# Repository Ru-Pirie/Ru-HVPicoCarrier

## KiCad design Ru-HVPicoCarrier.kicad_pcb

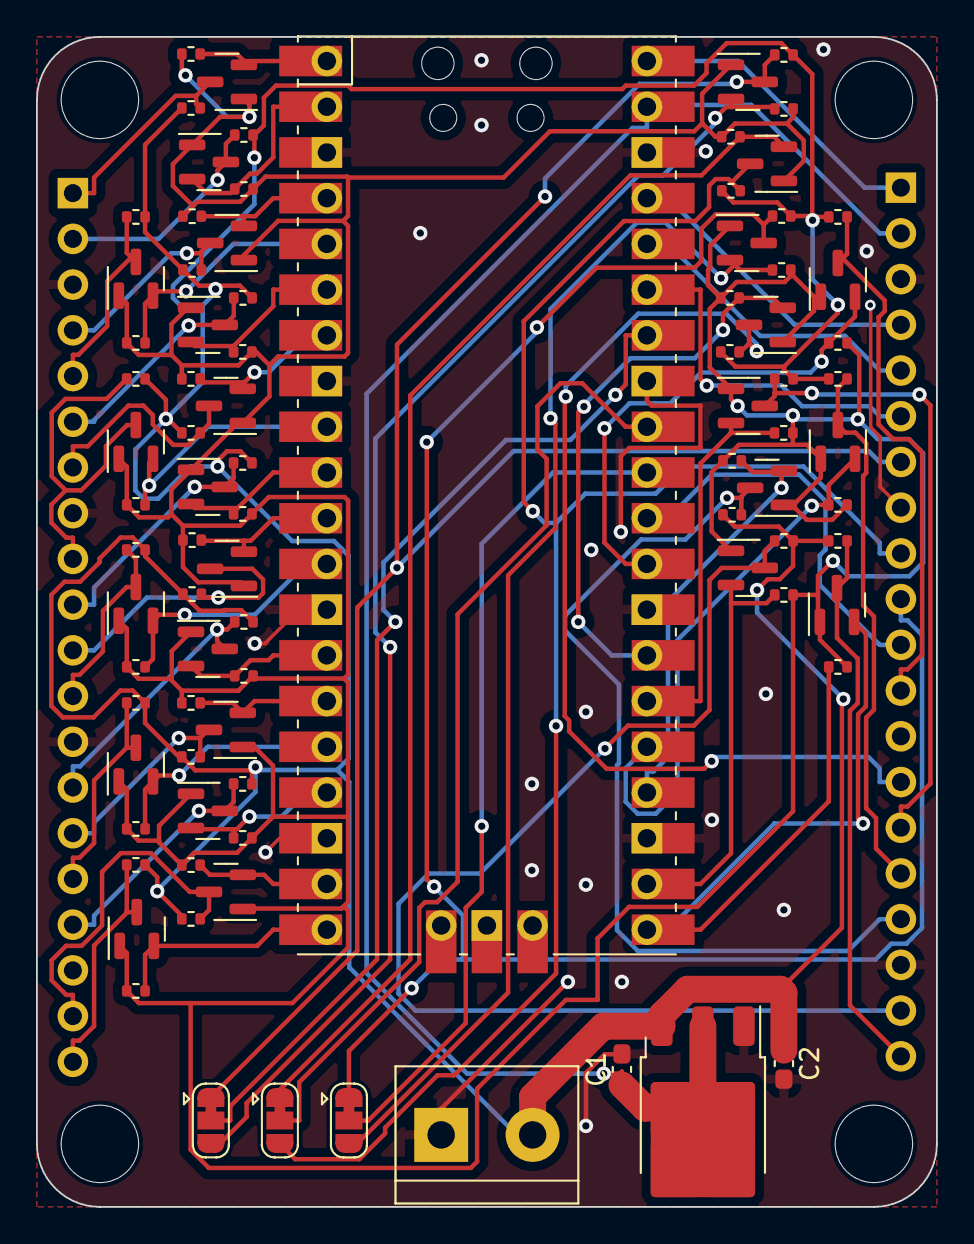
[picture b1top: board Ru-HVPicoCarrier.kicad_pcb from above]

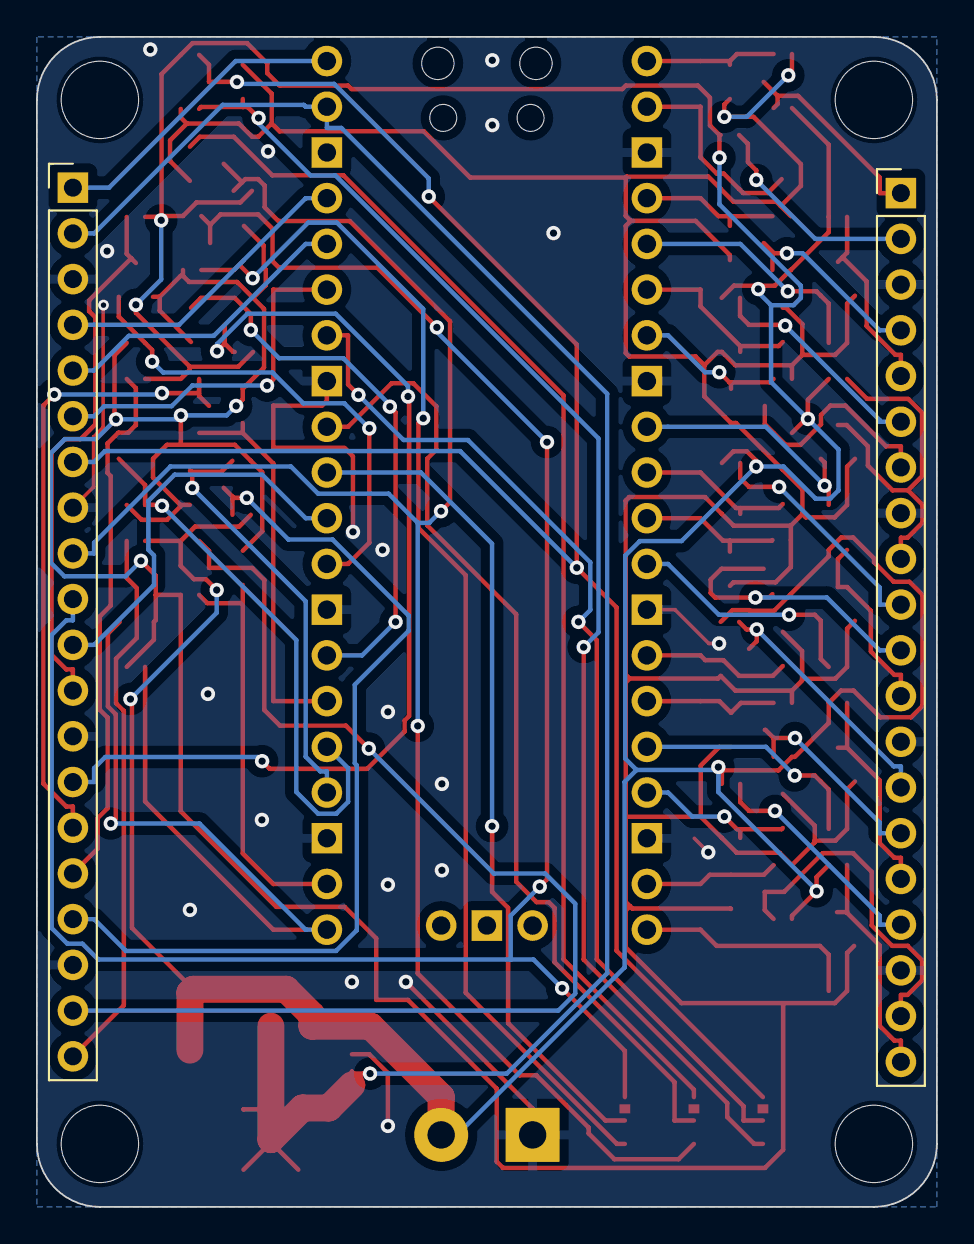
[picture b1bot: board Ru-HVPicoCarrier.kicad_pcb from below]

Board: 2 copper layers, 50.0 x 65.0 mm, 92 parts (2 on the bottom side), 64 nets.

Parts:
C1: 47uF; C_0603_1608Metric_Pad1.08x0.95mm_HandSolder
C2: 0.47uF; C_0603_1608Metric_Pad1.08x0.95mm_HandSolder
H1, H2, H3, H4: MountingHole; MountingHole_4.3mm_M4_ISO14580
J1, J2: 2.54mm header 01x20; PinHeader_1x20_P2.54mm_Vertical
J3: Screw_Terminal_01x02; TerminalBlock_bornier-2_P5.08mm
J4: PICO; RPi_Pico_SMD_TH
JP1, JP2, JP3: Jumper_3_Bridged12; SolderJumper-3_P1.3mm_Bridged12_RoundedPad1.0x1.5mm
Q1, Q2, Q3, Q4, Q5, Q6, Q7, Q8, Q9, Q10, Q11, Q12, Q13, Q14, Q15, Q16, Q17, Q18, Q19, Q20, Q21, Q22, Q23, Q24, Q25, Q26: BSN20; SOT-23
R1, R2, R3, R4, R5, R6, R7, R8, R9, R10, R11, R12, R13, R14, R15, R16, R17, R18, R19, R20, R21, R22, R23, R24, R25, R26, R27, R28, R29, R30, R31, R32, R33, R34, R35, R36, R37, R38, R39, R40, R41, R42, R43, R44, R45, R46, R47, R48, R49, R50, R51, R52: 10k; R_0402_1005Metric
U2: BA05CC0FP-E2; TO-252-3_TabPin2

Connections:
3V3_EN: J2.4, J4.37 (3V3_EN)
+3.3V: Q1.1 (G), Q2.1 (G), Q3.1 (G), Q4.1 (G), Q5.1 (G), Q6.1 (G), Q7.1 (G), Q8.1 (G), Q9.1 (G), Q10.1 (G), Q11.1 (G), Q12.1 (G), Q13.1 (G), Q14.1 (G), Q15.1 (G), Q16.1 (G), Q17.1 (G), Q18.1 (G), Q19.1 (G), Q20.1 (G), Q21.1 (G), Q22.1 (G), Q23.1 (G), Q24.1 (G), Q25.1 (G), Q26.1 (G), R2.2, R4.2, R6.2, R8.2, R10.2, R12.2, R14.2, R16.2, R18.2, R20.2, R22.2, R24.2, R26.2, R28.2, R30.2, R32.2, R34.2, R36.2, R38.2, R40.2, R42.2, R44.2, R46.2, R48.2, R50.2, R52.2
+3V3: J2.5, J4.36 (3V3(OUT))
+VDC: C2.1, J3.2, R1.2, R3.2, R5.2, R7.2, R9.2, R11.2, R13.2, R15.2, R17.2, R19.2, R21.2, R23.2, R25.2, R27.2, R29.2, R31.2, R33.2, R35.2, R37.2, R39.2, R41.2, R43.2, R45.2, R47.2, R49.2, R51.2, U2.3 (VI)
ADC_REF: J2.6, J4.35 (ADC_VREF)
GND: C1.2, C2.2, J1.3, J1.8, J1.13, J1.18, J2.3, J2.8, J2.13, J2.18, J3.1, J4.3 (GND_1), J4.8 (GND_2), J4.13 (GND_3), J4.18 (GND_4), J4.23 (GND_5), J4.28 (GND_6), J4.33 (GND_7), J4.38 (GND_8), U2.1 (GND)
IN0: J4.1 (GP0), Q1.2 (S), R2.1
IN1: J4.2 (GP1), Q2.2 (S), R4.1
IN2: J4.4 (GP2), Q3.2 (S), R6.1
IN3: J4.5 (GP3), Q4.2 (S), R8.1
IN4: J4.6 (GP4), Q5.2 (S), R10.1
IN5: J4.7 (GP5), Q6.2 (S), R12.1
IN6: J4.9 (GP6), Q7.2 (S), R14.1
IN7: J4.10 (GP7), Q8.2 (S), R16.1
IN8: J4.11 (GP8), Q9.2 (S), R18.1
IN9: J4.12 (GP9), Q10.2 (S), R20.1
IN10: J4.14 (GP10), Q11.2 (S), R22.1
IN11: J4.15 (GP11), Q12.2 (S), R24.1
IN12: J4.16 (GP12), Q13.2 (S), R26.1
IN13: J4.17 (GP13), Q14.2 (S), R28.1
IN14: J4.19 (GP14), Q15.2 (S), R30.1
IN15: J4.20 (GP15), Q16.2 (S), R32.1
IN16: J4.21 (GP16), Q17.2 (S), R34.1
IN17: J4.22 (GP17), Q18.2 (S), R36.1
IN18: J4.24 (GP18), Q19.2 (S), R38.1
IN19: J4.25 (GP19), Q20.2 (S), R40.1
IN20: J4.26 (GP20), Q21.2 (S), R42.1
IN21: J4.27 (GP21), Q22.2 (S), R44.1
IN22: J4.29 (GP22), Q23.2 (S), R46.1
IN26: J4.31 (GP26_A0), JP1.2 (C)
IN27: J4.32 (GP27_A1), JP2.2 (C)
IN28: J4.34 (GP28_A2), JP3.2 (C)
OUT0: J1.1, Q1.3 (D), R1.1
OUT1: J1.2, Q2.3 (D), R3.1
OUT2: J1.4, Q3.3 (D), R5.1
OUT3: J1.5, Q4.3 (D), R7.1
OUT4: J1.6, Q5.3 (D), R9.1
OUT5: J1.7, Q6.3 (D), R11.1
OUT6: J1.9, Q7.3 (D), R13.1
OUT7: J1.10, Q8.3 (D), R15.1
OUT8: J1.11, Q9.3 (D), R17.1
OUT9: J1.12, Q10.3 (D), R19.1
OUT10: J1.14, Q11.3 (D), R21.1
OUT11: J1.15, Q12.3 (D), R23.1
OUT12: J1.16, Q13.3 (D), R25.1
OUT13: J1.17, Q14.3 (D), R27.1
OUT14: J1.19, Q15.3 (D), R29.1
OUT15: J1.20, Q16.3 (D), R31.1
OUT16: J2.20, Q17.3 (D), R33.1
OUT17: J2.19, Q18.3 (D), R35.1
OUT18: J2.17, Q19.3 (D), R37.1
OUT19: J2.16, Q20.3 (D), R39.1
OUT20: J2.15, Q21.3 (D), R41.1
OUT21: J2.14, Q22.3 (D), R43.1
OUT22: J2.12, Q23.3 (D), R45.1
OUT26: J2.10, JP1.1 (A), Q24.3 (D), R47.1
OUT27: J2.9, JP2.3 (B), Q25.3 (D), R49.1
OUT28: J2.7, JP3.1 (A), Q26.3 (D), R51.1
RUN: J2.11, J4.30 (RUN)
SHIFTA: JP1.3 (B), Q24.2 (S), R48.1
SHIFTB: JP2.1 (A), Q25.2 (S), R50.1
SHIFTC: JP3.3 (B), Q26.2 (S), R52.1
VBUS: J2.1, J4.40 (VBUS)
VSYS: C1.1, J2.2, J4.39 (VSYS), U2.2 (VO)

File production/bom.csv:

Designator,Footprint,Quantity,Value,LCSC Part #
C1,1210,1,47uF,
C2,1206,1,0.47uF,
"J1, J2",PinHeader_1x20_P2.54mm_Vertical,2,2.54mm header 01x20, 
J3,TerminalBlock_bornier-2_P5.08mm,1,Screw_Terminal_01x02,
J4,RPi_Pico_SMD_TH,1,PICO,
"JP1_2, JP1, JP2, JP3",SolderJumper-3_P1.3mm_Bridged12_RoundedPad1.0x1.5mm,4,Jumper_3_Bridged12,
"Q1, Q10, Q11, Q12, Q13, Q14, Q15, Q16, Q17, Q18, Q19, Q2, Q20, Q21, Q22, Q23, Q24, Q25, Q26, Q3, Q4, Q5, Q6, Q7, Q8, Q9",SOT-23,26,BSN20,
"R1, R10, R11, R12, R13, R14, R15, R16, R17, R18, R19, R2, R20, R21, R22, R23, R24, R25, R26, R27, R28, R29, R3, R30, R31, R32, R33, R34, R35, R36, R37, R38, R39, R4, R40, R41, R42, R43, R44, R45, R46, R47, R48, R49, R5, R50, R51, R52, R6, R7, R8, R9",0402,52,10k,
U2,TO-252-3_TabPin2,1,BA05CC0FP-E2,
